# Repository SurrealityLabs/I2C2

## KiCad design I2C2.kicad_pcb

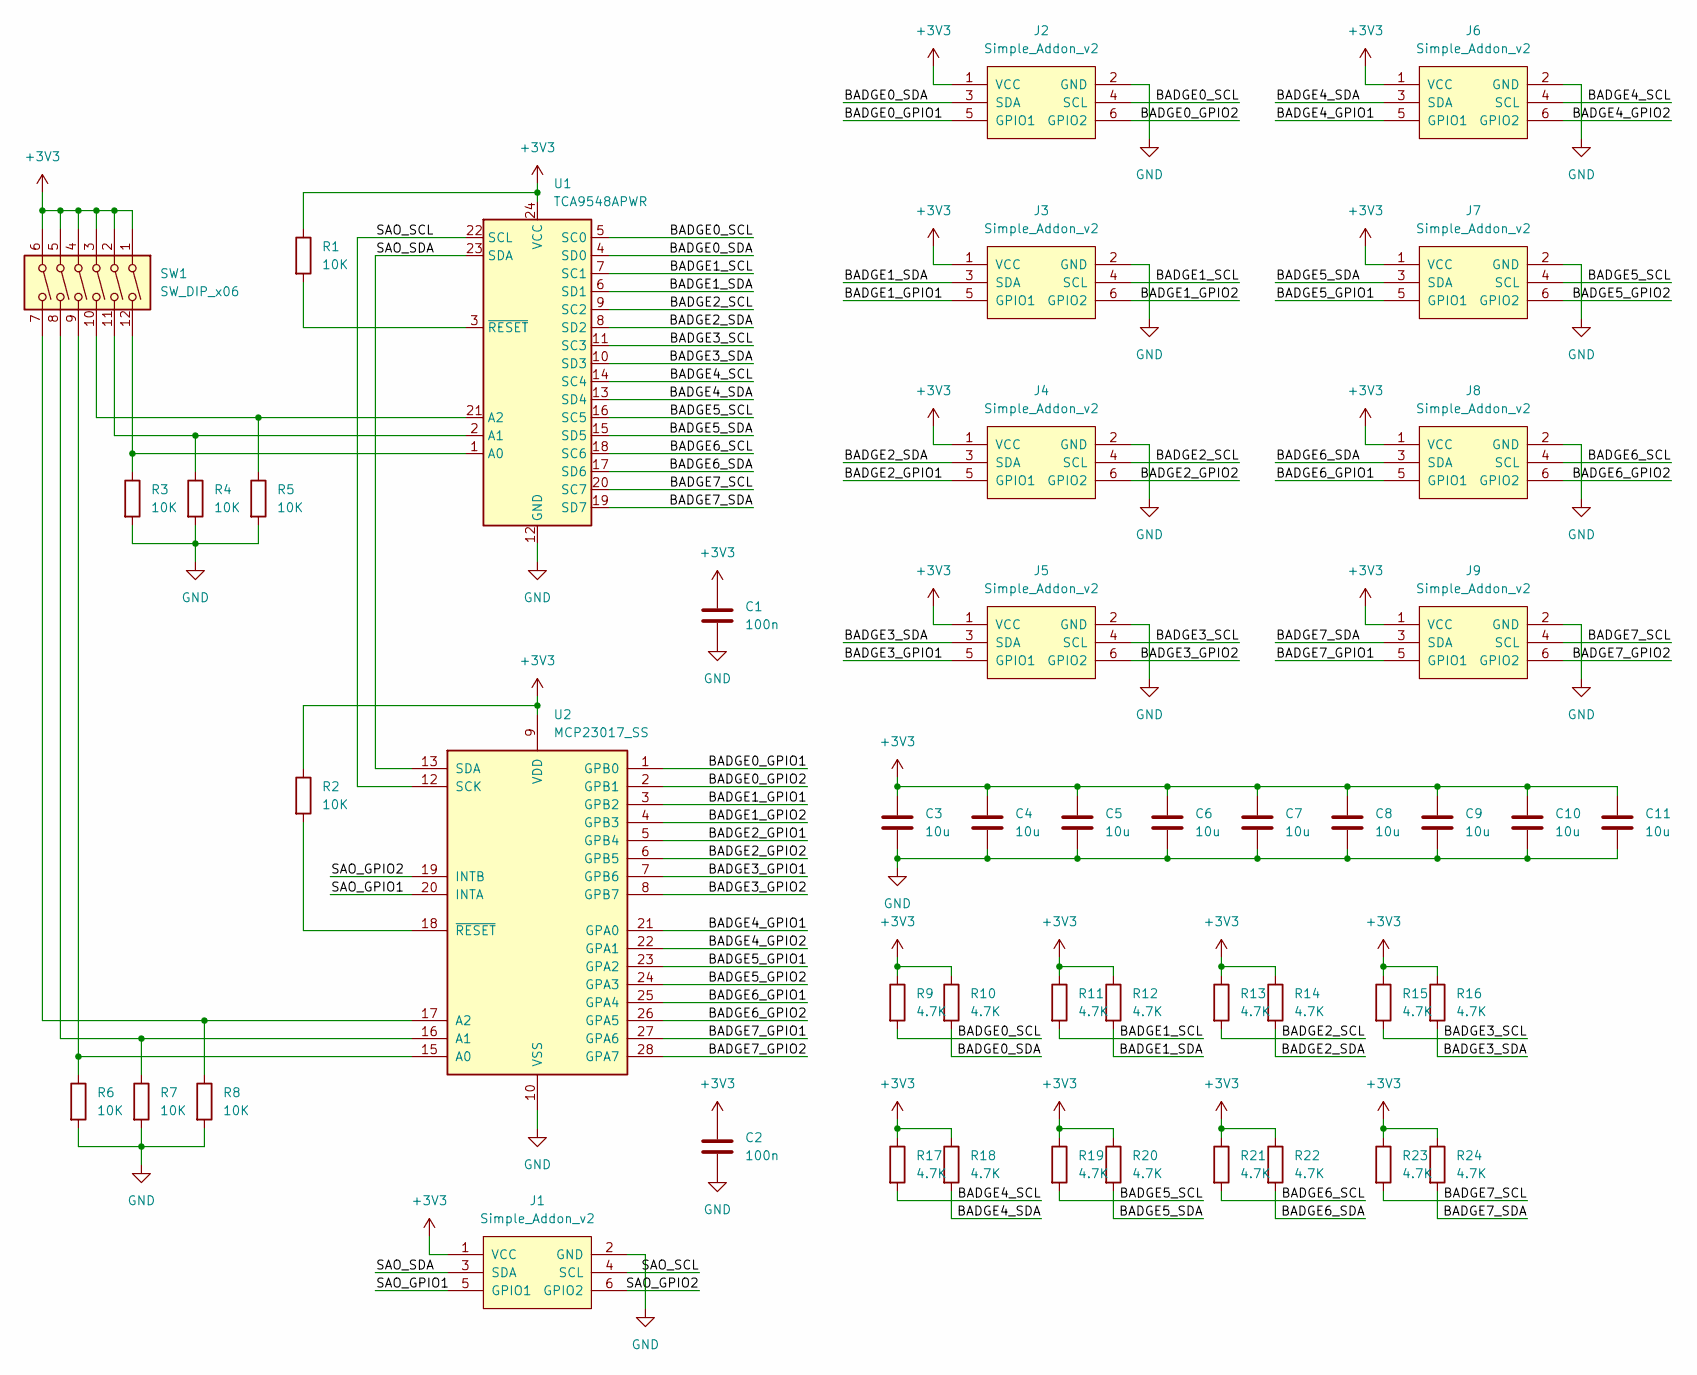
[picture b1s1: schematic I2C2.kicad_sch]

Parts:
C1, C2: 100n; C_0603_1608Metric_Pad1.08x0.95mm_HandSolder
C3, C4, C5, C6, C7, C8, C9, C10, C11: 10u; C_0805_2012Metric_Pad1.18x1.45mm_HandSolder
J1: Simple_Addon_v2; Simple_Addon_v2-SAO-2x3
J2, J3, J4, J5, J6, J7, J8, J9: Simple_Addon_v2; Simple_Addon_v2-BADGE-2x3
R1, R2, R3, R4, R5, R6, R7, R8: 10K; R_0603_1608Metric_Pad0.98x0.95mm_HandSolder
R9, R10, R11, R12, R13, R14, R15, R16, R17, R18, R19, R20, R21, R22, R23, R24: 4.7K; R_0603_1608Metric_Pad0.98x0.95mm_HandSolder
SW1: SW_DIP_x06; SW_DIP_SPSTx06_Slide_Copal_CHS-06B_W7.62mm_P1.27mm
U1: TCA9548APWR; TSSOP-24_4.4x7.8mm_P0.65mm
U2: MCP23017_SS; SSOP-28_5.3x10.2mm_P0.65mm

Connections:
+3V3: C1.1, C2.1, C3.1, C4.1, C5.1, C6.1, C7.1, C8.1, C9.1, C10.1, C11.1, J1.1 (VCC), J2.1 (VCC), J3.1 (VCC), J4.1 (VCC), J5.1 (VCC), J6.1 (VCC), J7.1 (VCC), J8.1 (VCC), J9.1 (VCC), R1.1, R2.1, R9.1, R10.1, R11.1, R12.1, R13.1, R14.1, R15.1, R16.1, R17.1, R18.1, R19.1, R20.1, R21.1, R22.1, R23.1, R24.1, SW1.1, SW1.2, SW1.3, SW1.4, SW1.5, SW1.6, U1.24 (VCC), U2.9 (VDD)
/BADGE0_GPIO1: J2.5 (GPIO1), U2.1 (GPB0)
/BADGE0_GPIO2: J2.6 (GPIO2), U2.2 (GPB1)
/BADGE0_SCL: J2.4 (SCL), R9.2, U1.5 (SC0)
/BADGE0_SDA: J2.3 (SDA), R10.2, U1.4 (SD0)
/BADGE1_GPIO1: J3.5 (GPIO1), U2.3 (GPB2)
/BADGE1_GPIO2: J3.6 (GPIO2), U2.4 (GPB3)
/BADGE1_SCL: J3.4 (SCL), R11.2, U1.7 (SC1)
/BADGE1_SDA: J3.3 (SDA), R12.2, U1.6 (SD1)
/BADGE2_GPIO1: J4.5 (GPIO1), U2.5 (GPB4)
/BADGE2_GPIO2: J4.6 (GPIO2), U2.6 (GPB5)
/BADGE2_SCL: J4.4 (SCL), R13.2, U1.9 (SC2)
/BADGE2_SDA: J4.3 (SDA), R14.2, U1.8 (SD2)
/BADGE3_GPIO1: J5.5 (GPIO1), U2.7 (GPB6)
/BADGE3_GPIO2: J5.6 (GPIO2), U2.8 (GPB7)
/BADGE3_SCL: J5.4 (SCL), R15.2, U1.11 (SC3)
/BADGE3_SDA: J5.3 (SDA), R16.2, U1.10 (SD3)
/BADGE4_GPIO1: J6.5 (GPIO1), U2.21 (GPA0)
/BADGE4_GPIO2: J6.6 (GPIO2), U2.22 (GPA1)
/BADGE4_SCL: J6.4 (SCL), R17.2, U1.14 (SC4)
/BADGE4_SDA: J6.3 (SDA), R18.2, U1.13 (SD4)
/BADGE5_GPIO1: J7.5 (GPIO1), U2.23 (GPA2)
/BADGE5_GPIO2: J7.6 (GPIO2), U2.24 (GPA3)
/BADGE5_SCL: J7.4 (SCL), R19.2, U1.16 (SC5)
/BADGE5_SDA: J7.3 (SDA), R20.2, U1.15 (SD5)
/BADGE6_GPIO1: J8.5 (GPIO1), U2.25 (GPA4)
/BADGE6_GPIO2: J8.6 (GPIO2), U2.26 (GPA5)
/BADGE6_SCL: J8.4 (SCL), R21.2, U1.18 (SC6)
/BADGE6_SDA: J8.3 (SDA), R22.2, U1.17 (SD6)
/BADGE7_GPIO1: J9.5 (GPIO1), U2.27 (GPA6)
/BADGE7_GPIO2: J9.6 (GPIO2), U2.28 (GPA7)
/BADGE7_SCL: J9.4 (SCL), R23.2, U1.20 (SC7)
/BADGE7_SDA: J9.3 (SDA), R24.2, U1.19 (SD7)
/SAO_GPIO1: J1.5 (GPIO1), U2.20 (INTA)
/SAO_GPIO2: J1.6 (GPIO2), U2.19 (INTB)
/SAO_SCL: J1.4 (SCL), U1.22 (SCL), U2.12 (SCK)
/SAO_SDA: J1.3 (SDA), U1.23 (SDA), U2.13 (SDA)
GND: C1.2, C2.2, C3.2, C4.2, C5.2, C6.2, C7.2, C8.2, C9.2, C10.2, C11.2, J1.2 (GND), J2.2 (GND), J3.2 (GND), J4.2 (GND), J5.2 (GND), J6.2 (GND), J7.2 (GND), J8.2 (GND), J9.2 (GND), R3.2, R4.2, R5.2, R6.2, R7.2, R8.2, U1.12 (GND), U2.10 (VSS)
unnamed: R3.1, SW1.12, U1.1 (A0)
unnamed: R4.1, SW1.11, U1.2 (A1)
unnamed: R5.1, SW1.10, U1.21 (A2)
unnamed: R1.2, U1.3 (~RESET)
unnamed: R6.1, SW1.9, U2.15 (A0)
unnamed: R7.1, SW1.8, U2.16 (A1)
unnamed: R8.1, SW1.7, U2.17 (A2)
unnamed: R2.2, U2.18 (~RESET)

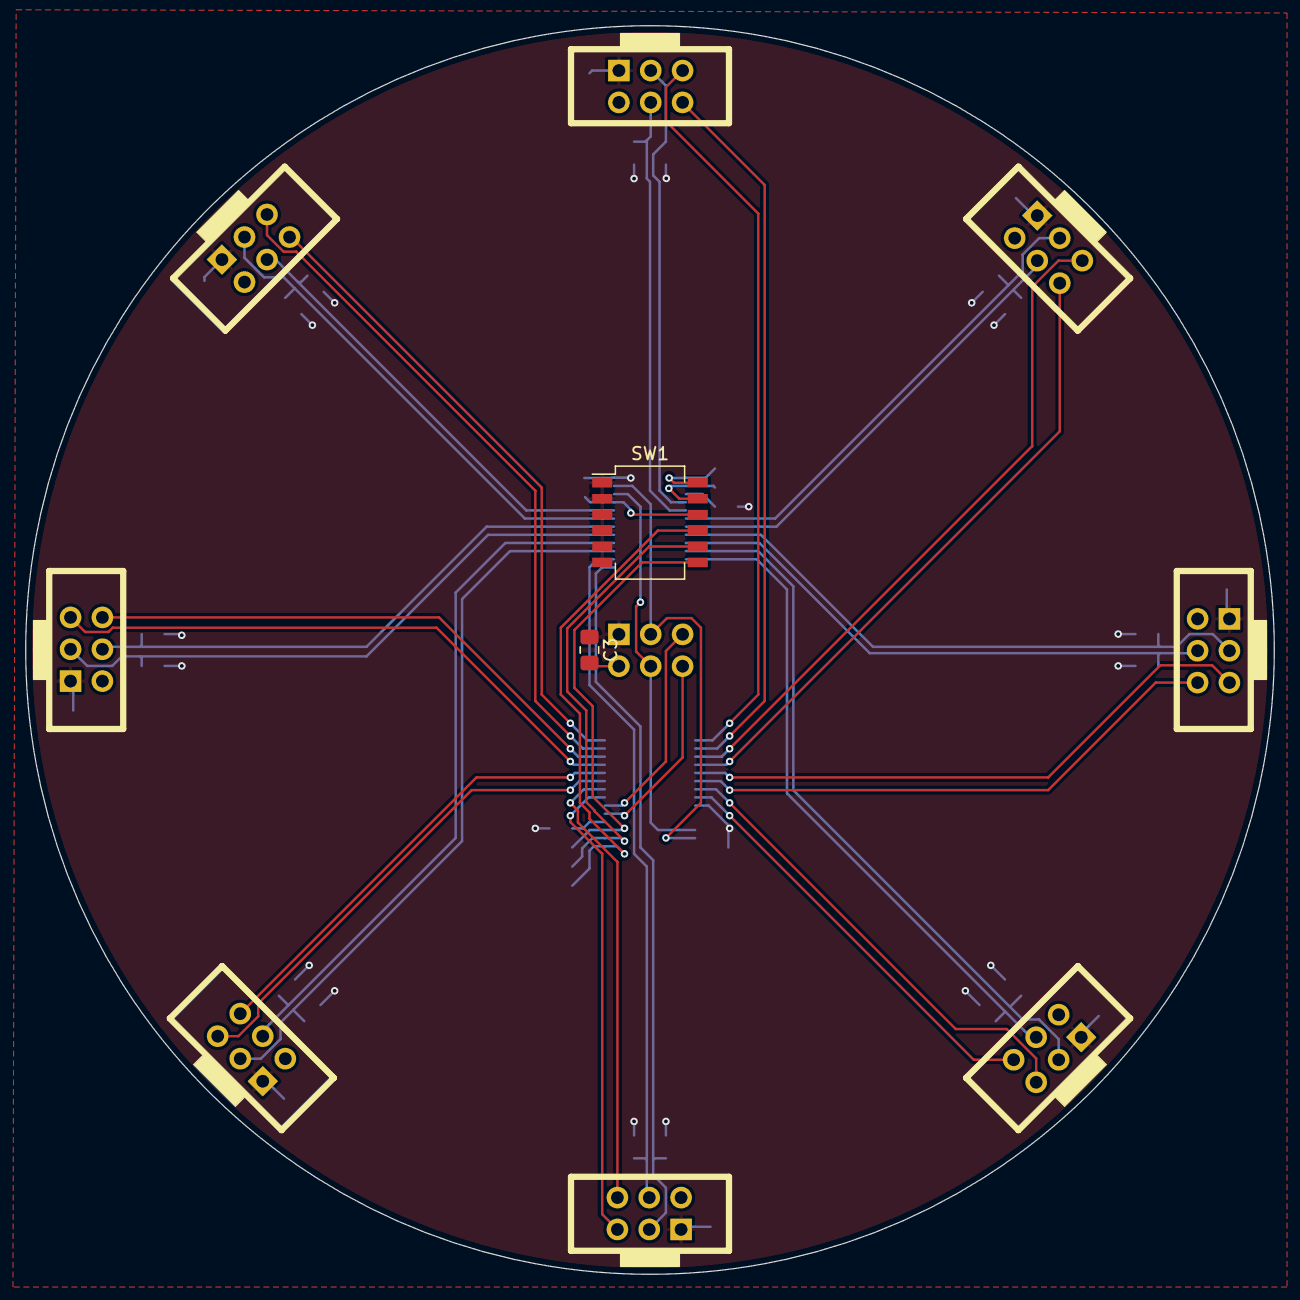
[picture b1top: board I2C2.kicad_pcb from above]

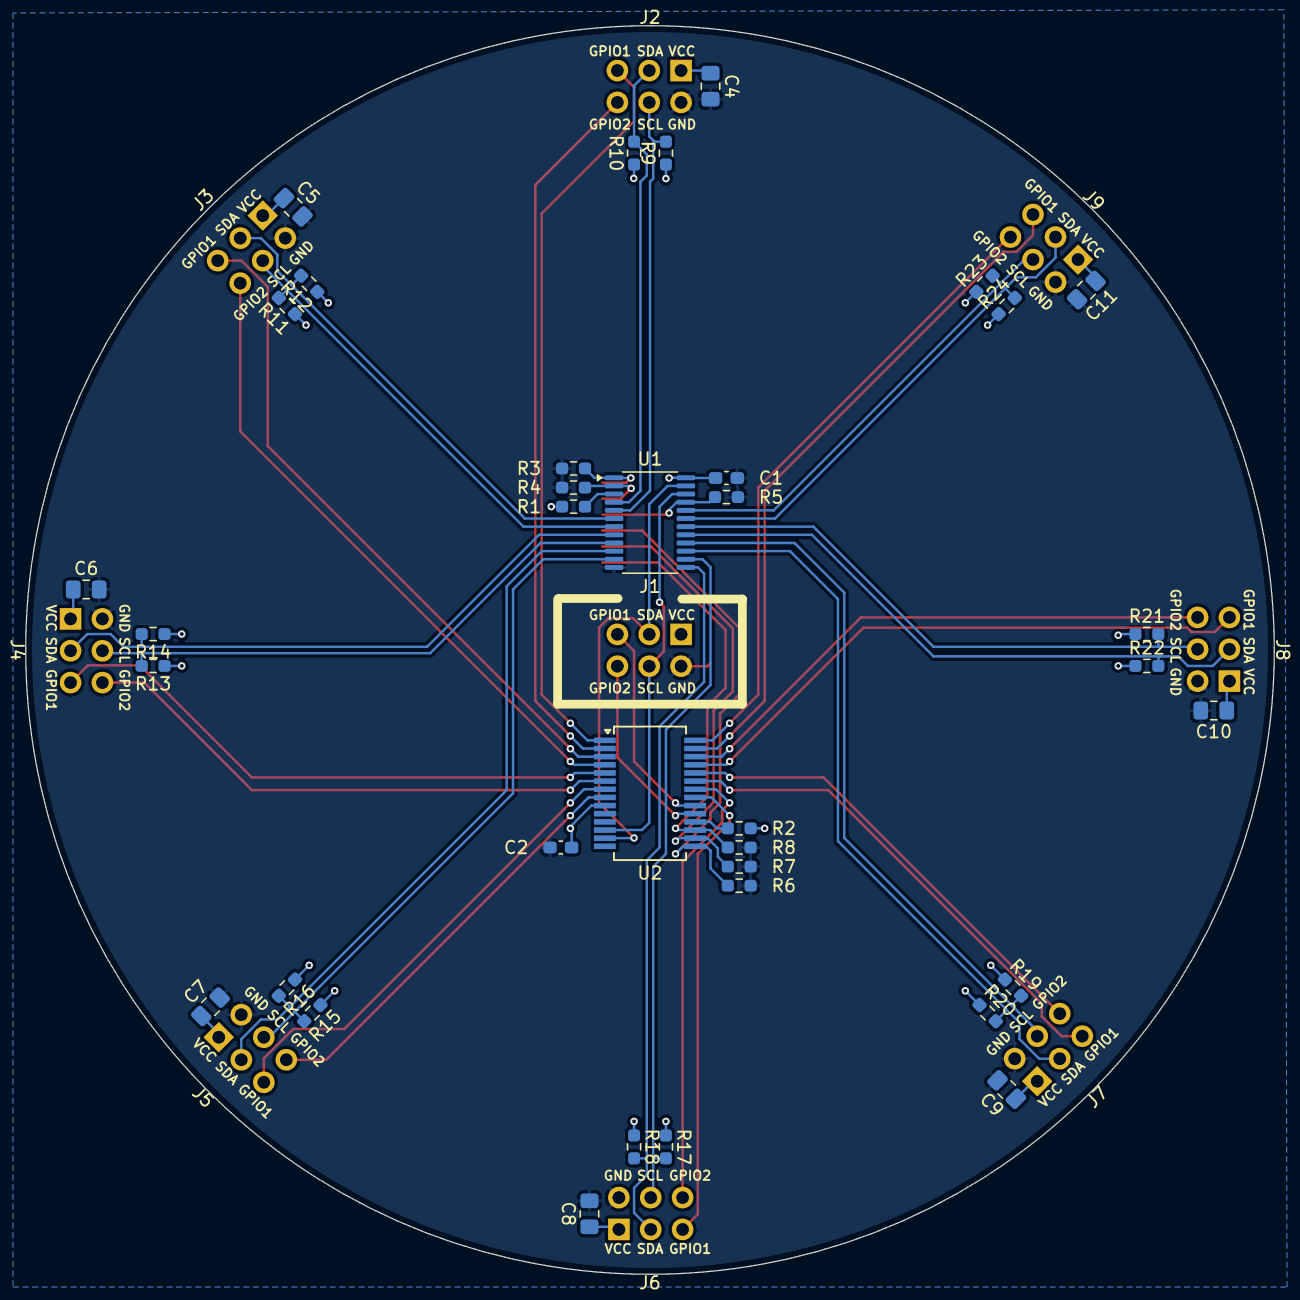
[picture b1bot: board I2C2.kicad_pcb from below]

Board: 2 copper layers, 99.6 x 99.6 mm, 47 parts (36 on the bottom side), 46 nets.

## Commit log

2024-11-20 Adding first attempt at schematic and layout, needs cleanup
